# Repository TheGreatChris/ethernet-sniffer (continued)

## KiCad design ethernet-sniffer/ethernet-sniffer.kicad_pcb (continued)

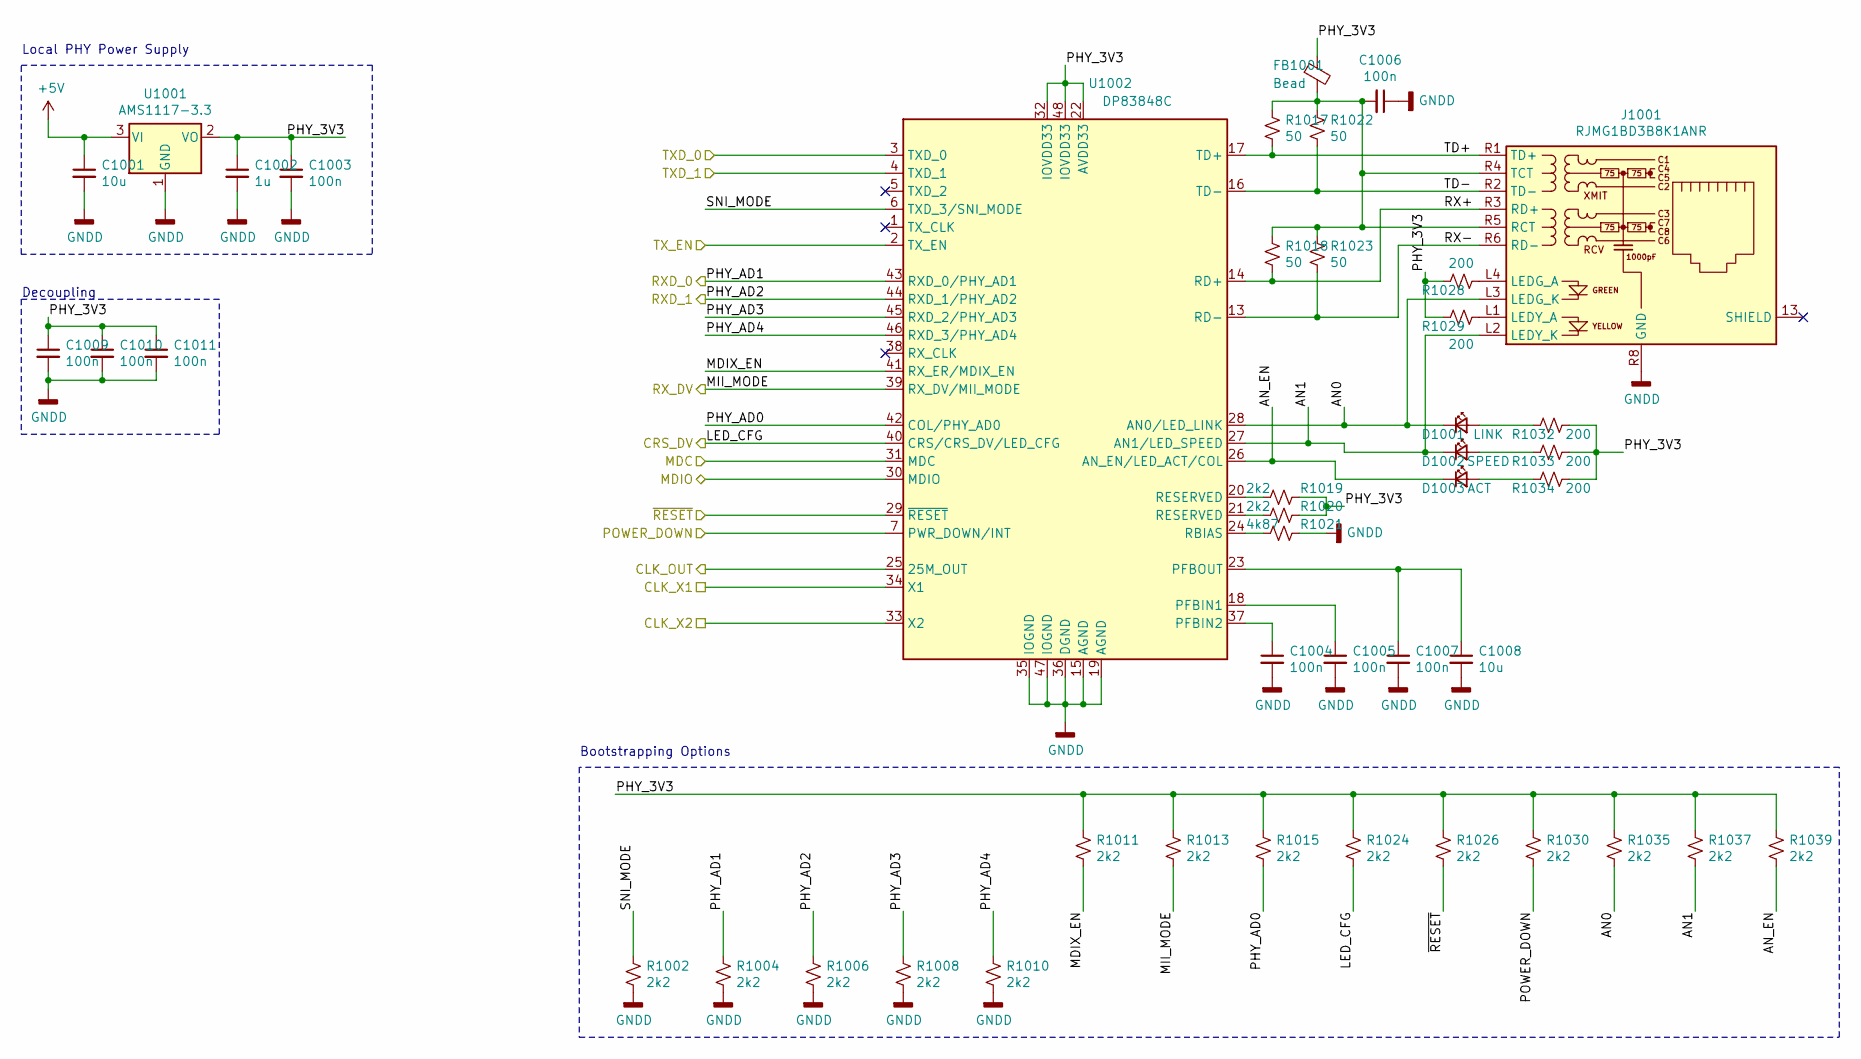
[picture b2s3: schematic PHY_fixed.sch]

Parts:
C801, C808: 10u; C_0402_1005Metric
C802: 1u; C_0402_1005Metric
C803, C804, C805, C806, C807, C1009, C1010, C1011: 100n; C_0402_1005Metric
D801: LINK; LED_0603_1608Metric
D802: SPEED; LED_0603_1608Metric
D803: ACT; LED_0603_1608Metric
FB801: Bead; L_0805_2012Metric
J801: RJMG1BD3B8K1ANR; RJ45_Amphenol_RJMG1BD3B8K1ANR
R802, R804, R806, R808, R810, R811, R813, R815, R819, R820, R824, R826, R830, R835, R837, R839: 2k2; R_0402_1005Metric
R817, R818, R822, R823: 50; R_0402_1005Metric
R821: 4k87; R_0402_1005Metric
R828, R829, R832, R833, R834: 200; R_0402_1005Metric
U801: AMS1117-3.3; SOT-223-3_TabPin2
U802: DP83848C; LQFP-48_7x7mm_P0.5mm

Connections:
+5V: C801.1, U801.3 (VI); also elsewhere on the board
/100BASETX-PHY 1/AN0: D801.1 (K), J801.L3 (LEDG_K), R835.2, U802.28 (AN0/LED_LINK)
/100BASETX-PHY 1/AN1: D802.1 (K), J801.L2 (LEDY_K), R837.2, U802.27 (AN1/LED_SPEED)
/100BASETX-PHY 1/AN_EN: D803.1 (K), R839.2, U802.26 (AN_EN/LED_ACT/COL)
/100BASETX-PHY 1/CLK_OUT: U802.25 (25M_OUT); also elsewhere on the board
/100BASETX-PHY 1/CLK_X2: U802.33 (X2)
/100BASETX-PHY 1/CRS_DV: R824.2, U802.40 (CRS/CRS_DV/LED_CFG); also elsewhere on the board
/100BASETX-PHY 1/MDC: U802.31 (MDC); also elsewhere on the board
/100BASETX-PHY 1/MDIO: U802.30 (MDIO); also elsewhere on the board
/100BASETX-PHY 1/MDIX_EN: R811.2, U802.41 (RX_ER/MDIX_EN)
/100BASETX-PHY 1/PHY_AD0: R815.2, U802.42 (COL/PHY_AD0)
/100BASETX-PHY 1/PHY_AD3: R808.1, U802.45 (RXD_2/PHY_AD3)
/100BASETX-PHY 1/PHY_AD4: R810.1, U802.46 (RXD_3/PHY_AD4)
/100BASETX-PHY 1/POWER_DOWN: R830.2, U802.7 (PWR_DOWN/INT)
/100BASETX-PHY 1/RX+: J801.R3 (RD+), R818.2, U802.14 (RD+)
/100BASETX-PHY 1/RX-: J801.R6 (RD-), R823.2, U802.13 (RD-)
/100BASETX-PHY 1/RX_DV: R813.2, U802.39 (RX_DV/MII_MODE)
/100BASETX-PHY 1/SNI_MODE: R802.1, U802.6 (TXD_3/SNI_MODE)
/100BASETX-PHY 1/TD+: J801.R1 (TD+), R817.2, U802.17 (TD+)
/100BASETX-PHY 1/TD-: J801.R2 (TD-), R822.2, U802.16 (TD-)
/100BASETX-PHY 1/~RESET: R826.2, U802.29 (~RESET~)
/FPGA/CLK_IN: U802.34 (X1); also elsewhere on the board
/STM32/PHY_RXD_0: R804.1, U802.43 (RXD_0/PHY_AD1); also elsewhere on the board
/STM32/PHY_RXD_1: R806.1, U802.44 (RXD_1/PHY_AD2); also elsewhere on the board
/STM32/PHY_TXD_0: U802.3 (TXD_0); also elsewhere on the board
/STM32/PHY_TXD_1: U802.4 (TXD_1); also elsewhere on the board
/STM32/PHY_TX_EN: U802.2 (TX_EN); also elsewhere on the board
GNDD: C801.2, C802.2, C803.2, C804.2, C805.2, C806.1, C807.2, C808.2, C1009.2, C1010.2, C1011.2, J801.R8 (GND), R802.2, R804.2, R806.2, R808.2, R810.2, R821.1, U801.1 (GND), U802.15 (AGND), U802.19 (AGND), U802.35 (IOGND), U802.36 (DGND), U802.47 (IOGND); also elsewhere on the board
unnamed: C804.1, U802.37 (PFBIN2)
unnamed: C805.1, U802.18 (PFBIN1)
unnamed: C806.2, FB801.2, J801.R4 (TCT), J801.R5 (RCT), R817.1, R818.1, R822.1, R823.1
unnamed: C807.1, C808.1, U802.23 (PFBOUT)
unnamed: D801.2 (A), R832.2
unnamed: D802.2 (A), R833.2
unnamed: D803.2 (A), R834.2
unnamed: J801.L1 (LEDY_A), R829.1
unnamed: J801.L4 (LEDG_A), R828.1
unnamed: R819.2, U802.20 (RESERVED)
unnamed: R820.2, U802.21 (RESERVED)
unnamed: R821.2, U802.24 (RBIAS)

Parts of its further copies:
C809, C810, C811, C903, C904, C905, C906, C907, C909, C910, C911, C1003, C1004, C1005, C1006, C1007, C1103, C1104, C1105, C1106, C1107, C1109, C1110, C1111: 100n; C_0402_1005Metric
C901, C908, C1001, C1008, C1101, C1108: 10u; C_0402_1005Metric
C902, C1002, C1102: 1u; C_0402_1005Metric
D901, D1001, D1101: LINK; LED_0603_1608Metric
D902, D1002, D1102: SPEED; LED_0603_1608Metric
D903, D1003, D1103: ACT; LED_0603_1608Metric
FB901, FB1001, FB1101: Bead; L_0805_2012Metric
J901, J1001, J1101: RJMG1BD3B8K1ANR; RJ45_Amphenol_RJMG1BD3B8K1ANR
R902, R904, R906, R908, R910, R911, R913, R915, R919, R920, R924, R926, R930, R935, R937, R939, R1002, R1004, R1006, R1008, R1010, R1011, R1013, R1015, R1019, R1020, R1024, R1026, R1030, R1035, R1037, R1039, R1102, R1104, R1106, R1108, R1110, R1111, R1113, R1115, R1119, R1120, R1124, R1126, R1130, R1135, R1137, R1139: 2k2; R_0402_1005Metric
R917, R918, R922, R923, R1017, R1018, R1022, R1023, R1117, R1118, R1122, R1123: 50; R_0402_1005Metric
R921, R1021, R1121: 4k87; R_0402_1005Metric
R928, R929, R932, R933, R934, R1028, R1029, R1032, R1033, R1034, R1128, R1129, R1132, R1133, R1134: 200; R_0402_1005Metric
U901, U1001, U1101: AMS1117-3.3; SOT-223-3_TabPin2
U902, U1002, U1102: DP83848C; LQFP-48_7x7mm_P0.5mm

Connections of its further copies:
+5V: C901.1, C1001.1, C1101.1, U901.3 (VI), U1001.3 (VI), U1101.3 (VI); also elsewhere on the board
/FPGA/PHY1_POWER_DOWN: R930.2, U902.7 (PWR_DOWN/INT); also elsewhere on the board
/FPGA/PHY1_RXD_0: R904.1, U902.43 (RXD_0/PHY_AD1); also elsewhere on the board
/FPGA/PHY1_RXD_1: R906.1, U902.44 (RXD_1/PHY_AD2); also elsewhere on the board
/FPGA/PHY1_RX_DV: R913.2, U902.39 (RX_DV/MII_MODE); also elsewhere on the board
/FPGA/PHY1_TXD_0: U902.3 (TXD_0); also elsewhere on the board
/FPGA/PHY1_TXD_1: U902.4 (TXD_1); also elsewhere on the board
/FPGA/PHY1_TX_EN: U902.2 (TX_EN); also elsewhere on the board
/FPGA/PHY2_POWER_DOWN: R1030.2, U1002.7 (PWR_DOWN/INT); also elsewhere on the board
/FPGA/PHY2_RXD_0: R1004.1, U1002.43 (RXD_0/PHY_AD1); also elsewhere on the board
/FPGA/PHY2_RXD_1: R1006.1, U1002.44 (RXD_1/PHY_AD2); also elsewhere on the board
/FPGA/PHY2_RX_DV: R1013.2, U1002.39 (RX_DV/MII_MODE); also elsewhere on the board
/FPGA/PHY2_TXD_0: U1002.3 (TXD_0); also elsewhere on the board
/FPGA/PHY2_TXD_1: U1002.4 (TXD_1); also elsewhere on the board
/FPGA/PHY2_TX_EN: U1002.2 (TX_EN); also elsewhere on the board
/FPGA/PHY3_POWER_DOWN: R1130.2, U1102.7 (PWR_DOWN/INT); also elsewhere on the board
/FPGA/PHY3_RXD_0: R1104.1, U1102.43 (RXD_0/PHY_AD1); also elsewhere on the board
/FPGA/PHY3_RXD_1: R1106.1, U1102.44 (RXD_1/PHY_AD2); also elsewhere on the board
/FPGA/PHY3_RX_DV: R1113.2, U1102.39 (RX_DV/MII_MODE); also elsewhere on the board
/FPGA/PHY3_TXD_0: U1102.3 (TXD_0); also elsewhere on the board
/FPGA/PHY3_TXD_1: U1102.4 (TXD_1); also elsewhere on the board
/FPGA/PHY3_TX_EN: U1102.2 (TX_EN); also elsewhere on the board
/FPGA/~PHY1_RESET: R926.2, U902.29 (~RESET~); also elsewhere on the board
/FPGA/~PHY2_RESET: R1026.2, U1002.29 (~RESET~); also elsewhere on the board
/FPGA/~PHY3_RESET: R1126.2, U1102.29 (~RESET~); also elsewhere on the board
/PHY1/AN0: D901.1 (K), J901.L3 (LEDG_K), R935.2, U902.28 (AN0/LED_LINK)
/PHY1/AN1: D902.1 (K), J901.L2 (LEDY_K), R937.2, U902.27 (AN1/LED_SPEED)
/PHY1/AN_EN: D903.1 (K), R939.2, U902.26 (AN_EN/LED_ACT/COL)
/PHY1/CLK_OUT: U902.25 (25M_OUT); also elsewhere on the board
/PHY1/CLK_X1: U902.34 (X1); also elsewhere on the board
/PHY1/CLK_X2: U902.33 (X2)
/PHY1/CRS_DV: R924.2, U902.40 (CRS/CRS_DV/LED_CFG); also elsewhere on the board
/PHY1/MDC: U902.31 (MDC); also elsewhere on the board
/PHY1/MDIO: U902.30 (MDIO); also elsewhere on the board
/PHY1/MDIX_EN: R911.2, U902.41 (RX_ER/MDIX_EN)
/PHY1/PHY_3V3: C902.1, C903.1, C909.1, C910.1, C911.1, FB901.1, R911.1, R913.1, R915.1, R919.1, R920.1, R924.1, R926.1, R928.2, R929.2, R930.1, R932.1, R933.1, R934.1, R935.1, R937.1, R939.1, U901.2 (VO), U902.22 (AVDD33), U902.32 (IOVDD33), U902.48 (IOVDD33)
/PHY1/PHY_AD0: R915.2, U902.42 (COL/PHY_AD0)
/PHY1/PHY_AD3: R908.1, U902.45 (RXD_2/PHY_AD3)
/PHY1/PHY_AD4: R910.1, U902.46 (RXD_3/PHY_AD4)
/PHY1/RX+: J901.R3 (RD+), R918.2, U902.14 (RD+)
/PHY1/RX-: J901.R6 (RD-), R923.2, U902.13 (RD-)
/PHY1/SNI_MODE: R902.1, U902.6 (TXD_3/SNI_MODE)
/PHY1/TD+: J901.R1 (TD+), R917.2, U902.17 (TD+)
/PHY1/TD-: J901.R2 (TD-), R922.2, U902.16 (TD-)
/PHY2/AN0: D1001.1 (K), J1001.L3 (LEDG_K), R1035.2, U1002.28 (AN0/LED_LINK)
/PHY2/AN1: D1002.1 (K), J1001.L2 (LEDY_K), R1037.2, U1002.27 (AN1/LED_SPEED)
/PHY2/AN_EN: D1003.1 (K), R1039.2, U1002.26 (AN_EN/LED_ACT/COL)
/PHY2/CLK_OUT: U1002.25 (25M_OUT); also elsewhere on the board
/PHY2/CLK_X1: U1002.34 (X1); also elsewhere on the board
/PHY2/CLK_X2: U1002.33 (X2)
/PHY2/CRS_DV: R1024.2, U1002.40 (CRS/CRS_DV/LED_CFG); also elsewhere on the board
/PHY2/MDC: U1002.31 (MDC); also elsewhere on the board
/PHY2/MDIO: U1002.30 (MDIO); also elsewhere on the board
/PHY2/MDIX_EN: R1011.2, U1002.41 (RX_ER/MDIX_EN)
/PHY2/PHY_AD0: R1015.2, U1002.42 (COL/PHY_AD0)
/PHY2/PHY_AD3: R1008.1, U1002.45 (RXD_2/PHY_AD3)
/PHY2/PHY_AD4: R1010.1, U1002.46 (RXD_3/PHY_AD4)
/PHY2/RX+: J1001.R3 (RD+), R1018.2, U1002.14 (RD+)
/PHY2/RX-: J1001.R6 (RD-), R1023.2, U1002.13 (RD-)
/PHY2/SNI_MODE: R1002.1, U1002.6 (TXD_3/SNI_MODE)
/PHY2/TD+: J1001.R1 (TD+), R1017.2, U1002.17 (TD+)
/PHY2/TD-: J1001.R2 (TD-), R1022.2, U1002.16 (TD-)
/PHY3/AN0: D1101.1 (K), J1101.L3 (LEDG_K), R1135.2, U1102.28 (AN0/LED_LINK)
/PHY3/AN1: D1102.1 (K), J1101.L2 (LEDY_K), R1137.2, U1102.27 (AN1/LED_SPEED)
/PHY3/AN_EN: D1103.1 (K), R1139.2, U1102.26 (AN_EN/LED_ACT/COL)
/PHY3/CLK_OUT: U1102.25 (25M_OUT); also elsewhere on the board
/PHY3/CLK_X1: U1102.34 (X1); also elsewhere on the board
/PHY3/CLK_X2: U1102.33 (X2)
/PHY3/CRS_DV: R1124.2, U1102.40 (CRS/CRS_DV/LED_CFG); also elsewhere on the board
/PHY3/MDC: U1102.31 (MDC); also elsewhere on the board
/PHY3/MDIO: U1102.30 (MDIO); also elsewhere on the board
/PHY3/MDIX_EN: R1111.2, U1102.41 (RX_ER/MDIX_EN)
/PHY3/PHY_3V3: C1102.1, C1103.1, C1109.1, C1110.1, C1111.1, FB1101.1, R1111.1, R1113.1, R1115.1, R1119.1, R1120.1, R1124.1, R1126.1, R1128.2, R1129.2, R1130.1, R1132.1, R1133.1, R1134.1, R1135.1, R1137.1, R1139.1, U1101.2 (VO), U1102.22 (AVDD33), U1102.32 (IOVDD33), U1102.48 (IOVDD33)
/PHY3/PHY_AD0: R1115.2, U1102.42 (COL/PHY_AD0)
/PHY3/PHY_AD3: R1108.1, U1102.45 (RXD_2/PHY_AD3)
/PHY3/PHY_AD4: R1110.1, U1102.46 (RXD_3/PHY_AD4)
/PHY3/RX+: J1101.R3 (RD+), R1118.2, U1102.14 (RD+)
/PHY3/RX-: J1101.R6 (RD-), R1123.2, U1102.13 (RD-)
/PHY3/SNI_MODE: R1102.1, U1102.6 (TXD_3/SNI_MODE)
/PHY3/TD+: J1101.R1 (TD+), R1117.2, U1102.17 (TD+)
/PHY3/TD-: J1101.R2 (TD-), R1122.2, U1102.16 (TD-)
GNDD: C809.2, C810.2, C811.2, C901.2, C902.2, C903.2, C904.2, C905.2, C906.1, C907.2, C908.2, C909.2, C910.2, C911.2, C1001.2, C1002.2, C1003.2, C1004.2, C1005.2, C1006.1, C1007.2, C1008.2, C1101.2, C1102.2, C1103.2, C1104.2, C1105.2, C1106.1, C1107.2, C1108.2, C1109.2, C1110.2, C1111.2, J901.R8 (GND), J1001.R8 (GND), J1101.R8 (GND), R902.2, R904.2, R906.2, R908.2, R910.2, R921.1, R1002.2, R1004.2, R1006.2, R1008.2, R1010.2, R1021.1, R1102.2, R1104.2, R1106.2, R1108.2, R1110.2, R1121.1, U901.1 (GND), U902.15 (AGND), U902.19 (AGND), U902.35 (IOGND), U902.36 (DGND), U902.47 (IOGND), U1001.1 (GND), U1002.15 (AGND), U1002.19 (AGND), U1002.35 (IOGND), U1002.36 (DGND), U1002.47 (IOGND), U1101.1 (GND), U1102.15 (AGND), U1102.19 (AGND), U1102.35 (IOGND), U1102.36 (DGND), U1102.47 (IOGND); also elsewhere on the board
unnamed: C904.1, U902.37 (PFBIN2)
unnamed: C905.1, U902.18 (PFBIN1)
unnamed: C906.2, FB901.2, J901.R4 (TCT), J901.R5 (RCT), R917.1, R918.1, R922.1, R923.1
unnamed: C907.1, C908.1, U902.23 (PFBOUT)
unnamed: C1004.1, U1002.37 (PFBIN2)
unnamed: C1005.1, U1002.18 (PFBIN1)
unnamed: C1006.2, FB1001.2, J1001.R4 (TCT), J1001.R5 (RCT), R1017.1, R1018.1, R1022.1, R1023.1
unnamed: C1007.1, C1008.1, U1002.23 (PFBOUT)
unnamed: C1104.1, U1102.37 (PFBIN2)
unnamed: C1105.1, U1102.18 (PFBIN1)
unnamed: C1106.2, FB1101.2, J1101.R4 (TCT), J1101.R5 (RCT), R1117.1, R1118.1, R1122.1, R1123.1
unnamed: C1107.1, C1108.1, U1102.23 (PFBOUT)
unnamed: D901.2 (A), R932.2
unnamed: D902.2 (A), R933.2
unnamed: D903.2 (A), R934.2
unnamed: D1001.2 (A), R1032.2
unnamed: D1002.2 (A), R1033.2
unnamed: D1003.2 (A), R1034.2
unnamed: D1101.2 (A), R1132.2
unnamed: D1102.2 (A), R1133.2
unnamed: D1103.2 (A), R1134.2
unnamed: J901.L1 (LEDY_A), R929.1
unnamed: J901.L4 (LEDG_A), R928.1
unnamed: J1001.L1 (LEDY_A), R1029.1
unnamed: J1001.L4 (LEDG_A), R1028.1
unnamed: J1101.L1 (LEDY_A), R1129.1
unnamed: J1101.L4 (LEDG_A), R1128.1
unnamed: R919.2, U902.20 (RESERVED)
unnamed: R920.2, U902.21 (RESERVED)
unnamed: R921.2, U902.24 (RBIAS)
unnamed: R1019.2, U1002.20 (RESERVED)
unnamed: R1020.2, U1002.21 (RESERVED)
unnamed: R1021.2, U1002.24 (RBIAS)
unnamed: R1119.2, U1102.20 (RESERVED)
unnamed: R1120.2, U1102.21 (RESERVED)
unnamed: R1121.2, U1102.24 (RBIAS)

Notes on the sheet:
Bootstrapping Options
Local PHY Power Supply
Decoupling

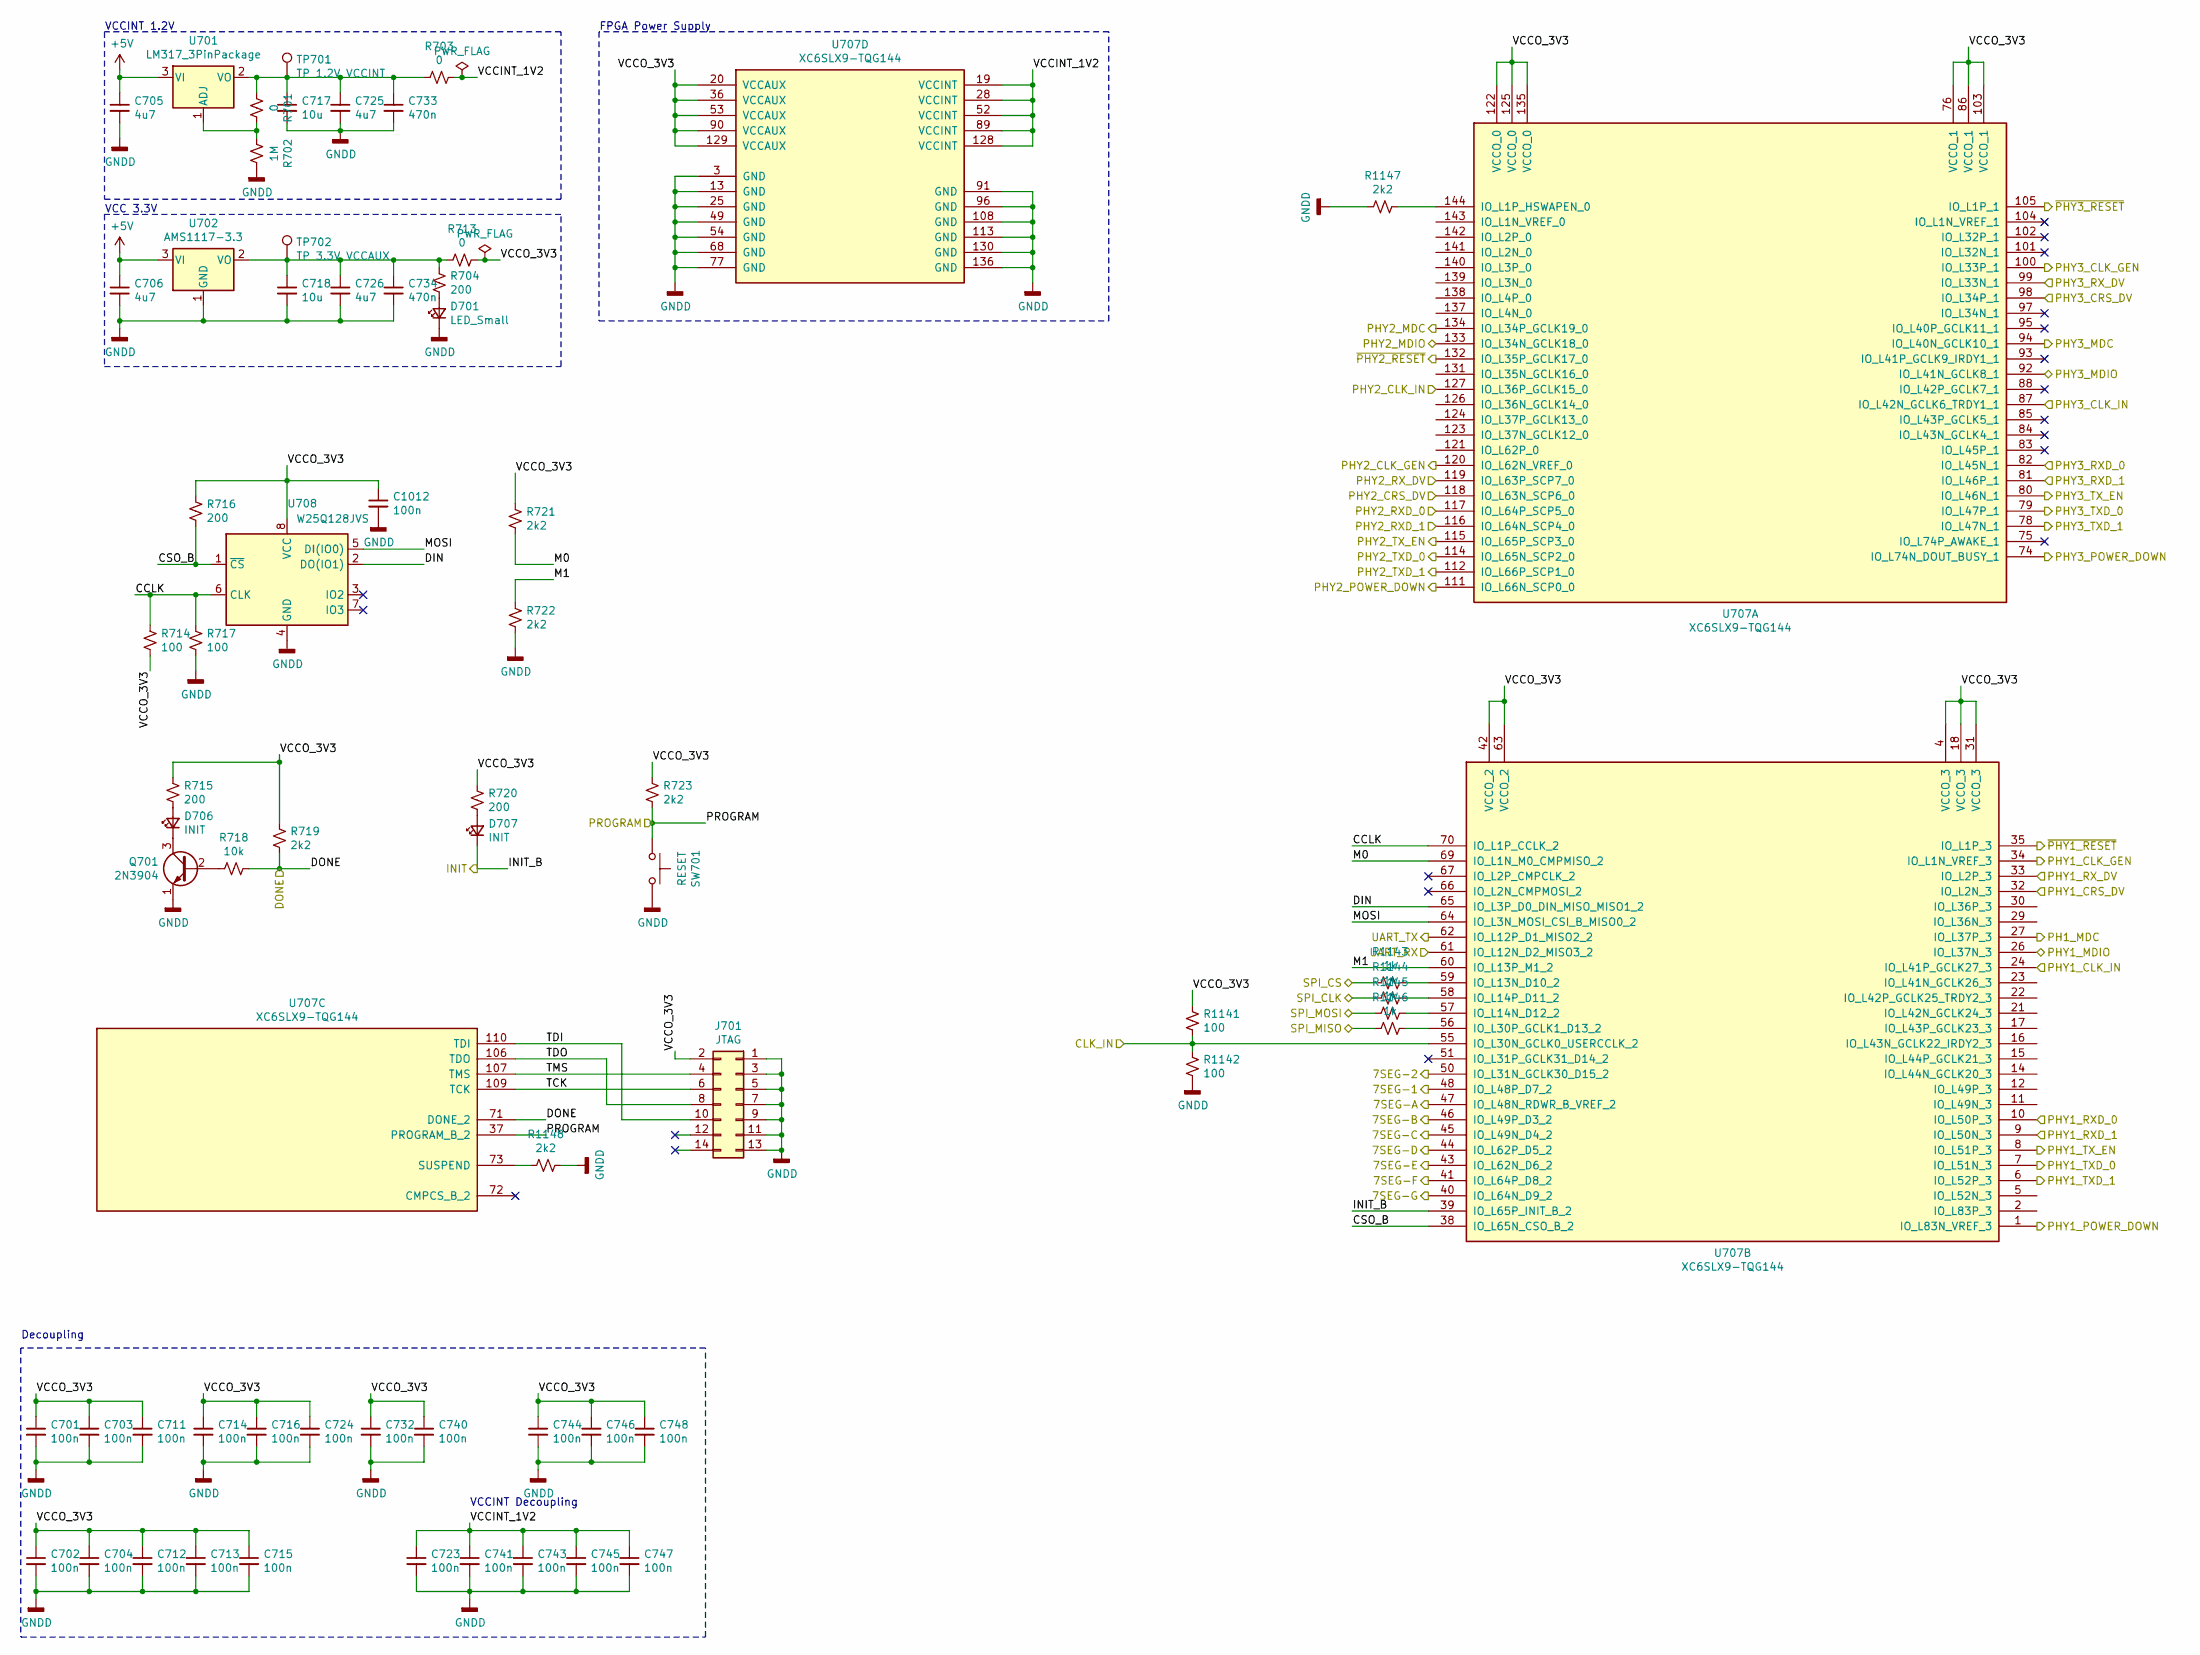
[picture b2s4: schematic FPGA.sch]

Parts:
C701, C702, C703, C704, C711, C712, C713, C714, C715, C716, C723, C724, C732, C740, C741, C743, C744, C745, C746, C747, C748, C1012: 100n; C_0402_1005Metric
C705, C706, C725, C726: 4u7; C_0402_1005Metric
C717, C718: 10u; C_0402_1005Metric
C733, C734: 470n; C_0402_1005Metric
D701: LED_Small; LED_0603_1608Metric
D706, D707: INIT; LED_0603_1608Metric
J701: JTAG; PinHeader_2x07_P2.54mm_Vertical
Q701: 2N3904; SOT-23
R701, R703, R713: 0; R_0402_1005Metric
R702: 1M; R_0402_1005Metric
R704, R715, R716, R720: 200; R_0402_1005Metric
R714, R717, R1141, R1142: 100; R_0402_1005Metric
R718: 10k; R_0402_1005Metric
R719, R721, R722, R723, R1147, R1148: 2k2; R_0402_1005Metric
R1143, R1144, R1145, R1146: 1k; R_0402_1005Metric
SW701: RESET; SW_Push_SPST_NO_Alps_SKRK
TP701: TP 1.2V VCCINT; TestPoint_Keystone_5015_Micro-Minature
TP702: TP 3.3V VCCAUX; TestPoint_Keystone_5015_Micro-Minature
U701: LM317_3PinPackage; TO-252-2
U702: AMS1117-3.3; SOT-223-3_TabPin2
U707: XC6SLX9-TQG144; LQFP-144_20x20mm_P0.5mm
U708: W25Q128JVS; SOIC-8_5.23x5.23mm_P1.27mm

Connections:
+5V: C705.1, C706.1, U701.3 (VI), U702.3 (VI); also elsewhere on the board
/7seg-display/7SEG-1: U707.48 (IO_L48P_D7_2); also elsewhere on the board
/7seg-display/7SEG-2: U707.50 (IO_L31N_GCLK30_D15_2); also elsewhere on the board
/7seg-display/7SEG-A: U707.47 (IO_L48N_RDWR_B_VREF_2); also elsewhere on the board
/7seg-display/7SEG-B: U707.46 (IO_L49P_D3_2); also elsewhere on the board
/7seg-display/7SEG-C: U707.45 (IO_L49N_D4_2); also elsewhere on the board
/7seg-display/7SEG-D: U707.44 (IO_L62P_D5_2); also elsewhere on the board
/7seg-display/7SEG-E: U707.43 (IO_L62N_D6_2); also elsewhere on the board
/7seg-display/7SEG-F: U707.41 (IO_L64P_D8_2); also elsewhere on the board
/7seg-display/7SEG-G: U707.40 (IO_L64N_D9_2); also elsewhere on the board
/FPGA/CCLK: R714.1, R717.1, U707.70 (IO_L1P_CCLK_2), U708.6 (CLK)
/FPGA/CLK_IN: R1141.2, R1142.1, U707.55 (IO_L30N_GCLK0_USERCCLK_2); also elsewhere on the board
/FPGA/CSO_B: R716.2, U707.38 (IO_L65N_CSO_B_2), U708.1 (~CS)
/FPGA/DIN: U707.65 (IO_L3P_D0_DIN_MISO_MISO1_2), U708.2 (DO(IO1))
/FPGA/DONE: R718.1, R719.2, U707.71 (DONE_2); also elsewhere on the board
/FPGA/M0: R721.2, U707.69 (IO_L1N_M0_CMPMISO_2)
/FPGA/M1: R722.1, U707.60 (IO_L13P_M1_2)
/FPGA/MOSI: U707.64 (IO_L3N_MOSI_CSI_B_MISO0_2), U708.5 (DI(IO0))
/FPGA/PHY1_POWER_DOWN: U707.1 (IO_L83N_VREF_3); also elsewhere on the board
/FPGA/PHY1_RXD_0: U707.10 (IO_L50P_3); also elsewhere on the board
/FPGA/PHY1_RXD_1: U707.9 (IO_L50N_3); also elsewhere on the board
/FPGA/PHY1_RX_DV: U707.33 (IO_L2P_3); also elsewhere on the board
/FPGA/PHY1_TXD_0: U707.7 (IO_L51N_3); also elsewhere on the board
/FPGA/PHY1_TXD_1: U707.6 (IO_L52P_3); also elsewhere on the board
/FPGA/PHY1_TX_EN: U707.8 (IO_L51P_3); also elsewhere on the board
/FPGA/PHY2_POWER_DOWN: U707.111 (IO_L66N_SCP0_0); also elsewhere on the board
/FPGA/PHY2_RXD_0: U707.117 (IO_L64P_SCP5_0); also elsewhere on the board
/FPGA/PHY2_RXD_1: U707.116 (IO_L64N_SCP4_0); also elsewhere on the board
/FPGA/PHY2_RX_DV: U707.119 (IO_L63P_SCP7_0); also elsewhere on the board
/FPGA/PHY2_TXD_0: U707.114 (IO_L65N_SCP2_0); also elsewhere on the board
/FPGA/PHY2_TXD_1: U707.112 (IO_L66P_SCP1_0); also elsewhere on the board
/FPGA/PHY2_TX_EN: U707.115 (IO_L65P_SCP3_0); also elsewhere on the board
/FPGA/PHY3_POWER_DOWN: U707.74 (IO_L74N_DOUT_BUSY_1); also elsewhere on the board
/FPGA/PHY3_RXD_0: U707.82 (IO_L45N_1); also elsewhere on the board
/FPGA/PHY3_RXD_1: U707.81 (IO_L46P_1); also elsewhere on the board
/FPGA/PHY3_RX_DV: U707.99 (IO_L33N_1); also elsewhere on the board
/FPGA/PHY3_TXD_0: U707.79 (IO_L47P_1); also elsewhere on the board
/FPGA/PHY3_TXD_1: U707.78 (IO_L47N_1); also elsewhere on the board
/FPGA/PHY3_TX_EN: U707.80 (IO_L46N_1); also elsewhere on the board
/FPGA/TCK: J701.6, U707.109 (TCK)
/FPGA/TDI: J701.10, U707.110 (TDI)
/FPGA/TDO: J701.8, U707.106 (TDO)
/FPGA/TMS: J701.4, U707.107 (TMS)
/FPGA/VCCINT_1V2: C723.1, C741.1, C743.1, C745.1, C747.1, R703.1, U707.19 (VCCINT), U707.28 (VCCINT), U707.52 (VCCINT), U707.89 (VCCINT), U707.128 (VCCINT)
/FPGA/VCCO_3V3: C701.1, C702.1, C703.1, C704.1, C711.1, C712.1, C713.1, C714.1, C715.1, C716.1, C724.1, C732.1, C740.1, C744.1, C746.1, C748.1, C1012.1, J701.2, R713.1, R714.2, R715.1, R716.1, R719.1, R720.1, R721.1, R723.1, R1141.1, U707.4 (VCCO_3), U707.18 (VCCO_3), U707.20 (VCCAUX), U707.31 (VCCO_3), U707.36 (VCCAUX), U707.42 (VCCO_2), U707.53 (VCCAUX), U707.63 (VCCO_2), U707.76 (VCCO_1), U707.86 (VCCO_1), U707.90 (VCCAUX), U707.103 (VCCO_1), U707.122 (VCCO_0), U707.125 (VCCO_0), U707.129 (VCCAUX), U707.135 (VCCO_0), U708.8 (VCC)
/FPGA/~PHY1_RESET: U707.35 (IO_L1P_3); also elsewhere on the board
/FPGA/~PHY2_RESET: U707.132 (IO_L35P_GCLK17_0); also elsewhere on the board
/FPGA/~PHY3_RESET: U707.105 (IO_L1P_1); also elsewhere on the board
/PHY1/CLK_OUT: U707.24 (IO_L41P_GCLK27_3); also elsewhere on the board
/PHY1/CLK_X1: U707.34 (IO_L1N_VREF_3); also elsewhere on the board
/PHY1/CRS_DV: U707.32 (IO_L2N_3); also elsewhere on the board
/PHY1/MDC: U707.27 (IO_L37P_3); also elsewhere on the board
/PHY1/MDIO: U707.26 (IO_L37N_3); also elsewhere on the board
/PHY2/CLK_OUT: U707.127 (IO_L36P_GCLK15_0); also elsewhere on the board
/PHY2/CLK_X1: U707.120 (IO_L62N_VREF_0); also elsewhere on the board
/PHY2/CRS_DV: U707.118 (IO_L63N_SCP6_0); also elsewhere on the board
/PHY2/MDC: U707.134 (IO_L34P_GCLK19_0); also elsewhere on the board
/PHY2/MDIO: U707.133 (IO_L34N_GCLK18_0); also elsewhere on the board
/PHY3/CLK_OUT: U707.87 (IO_L42N_GCLK6_TRDY1_1); also elsewhere on the board
/PHY3/CLK_X1: U707.100 (IO_L33P_1); also elsewhere on the board
/PHY3/CRS_DV: U707.98 (IO_L34P_1); also elsewhere on the board
/PHY3/MDC: U707.94 (IO_L40N_GCLK10_1); also elsewhere on the board
/PHY3/MDIO: U707.92 (IO_L41N_GCLK8_1); also elsewhere on the board
/STM32/FPGA_INIT: D707.1 (K), U707.39 (IO_L65P_INIT_B_2); also elsewhere on the board
/STM32/FPGA_PROGRAM: R723.2, SW701.1, U707.37 (PROGRAM_B_2); also elsewhere on the board
/STM32/SPI1_CS: R1143.2; also elsewhere on the board
/STM32/SPI1_MISO: R1145.2; also elsewhere on the board
/STM32/SPI1_MOSI: R1146.2; also elsewhere on the board
/STM32/SPI1_SCK: R1144.2; also elsewhere on the board
/USB-UART/UART-RX: U707.62 (IO_L12P_D1_MISO2_2); also elsewhere on the board
/USB-UART/UART-TX: U707.61 (IO_L12N_D2_MISO3_2); also elsewhere on the board
GNDD: C701.2, C702.2, C703.2, C704.2, C705.2, C706.2, C711.2, C712.2, C713.2, C714.2, C715.2, C716.2, C717.2, C718.2, C723.2, C724.2, C725.2, C726.2, C732.2, C733.2, C734.2, C740.2, C741.2, C743.2, C744.2, C745.2, C746.2, C747.2, C748.2, C1012.2, D701.1 (K), J701.1, J701.3, J701.5, J701.7, J701.9, J701.11, J701.13, Q701.1 (E), R702.1, R717.2, R722.2, R1142.2, R1147.2, R1148.1, SW701.2, U702.1 (GND), U707.3 (GND), U707.13 (GND), U707.25 (GND), U707.49 (GND), U707.54 (GND), U707.68 (GND), U707.77 (GND), U707.91 (GND), U707.96 (GND), U707.108 (GND), U707.113 (GND), U707.130 (GND), U707.136 (GND), U708.4 (GND); also elsewhere on the board
unnamed: C717.1, C725.1, C733.1, R701.2, R703.2, TP701.1, U701.2 (VO)
unnamed: C718.1, C726.1, C734.1, R704.1, R713.2, TP702.1, U702.2 (VO)
unnamed: D701.2 (A), R704.2
unnamed: D706.1 (K), Q701.3 (C)
unnamed: D706.2 (A), R715.2
unnamed: D707.2 (A), R720.2
unnamed: Q701.2 (B), R718.2
unnamed: R701.1, R702.2, U701.1 (ADJ)
unnamed: R1143.1, U707.59 (IO_L13N_D10_2)
unnamed: R1144.1, U707.58 (IO_L14P_D11_2)
unnamed: R1145.1, U707.57 (IO_L14N_D12_2)
unnamed: R1146.1, U707.56 (IO_L30P_GCLK1_D13_2)
unnamed: R1147.1, U707.144 (IO_L1P_HSWAPEN_0)
unnamed: R1148.2, U707.73 (SUSPEND)

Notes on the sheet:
Decoupling
VCCINT 1.2V
VCC 3.3V
VCCINT Decoupling
FPGA Power Supply

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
